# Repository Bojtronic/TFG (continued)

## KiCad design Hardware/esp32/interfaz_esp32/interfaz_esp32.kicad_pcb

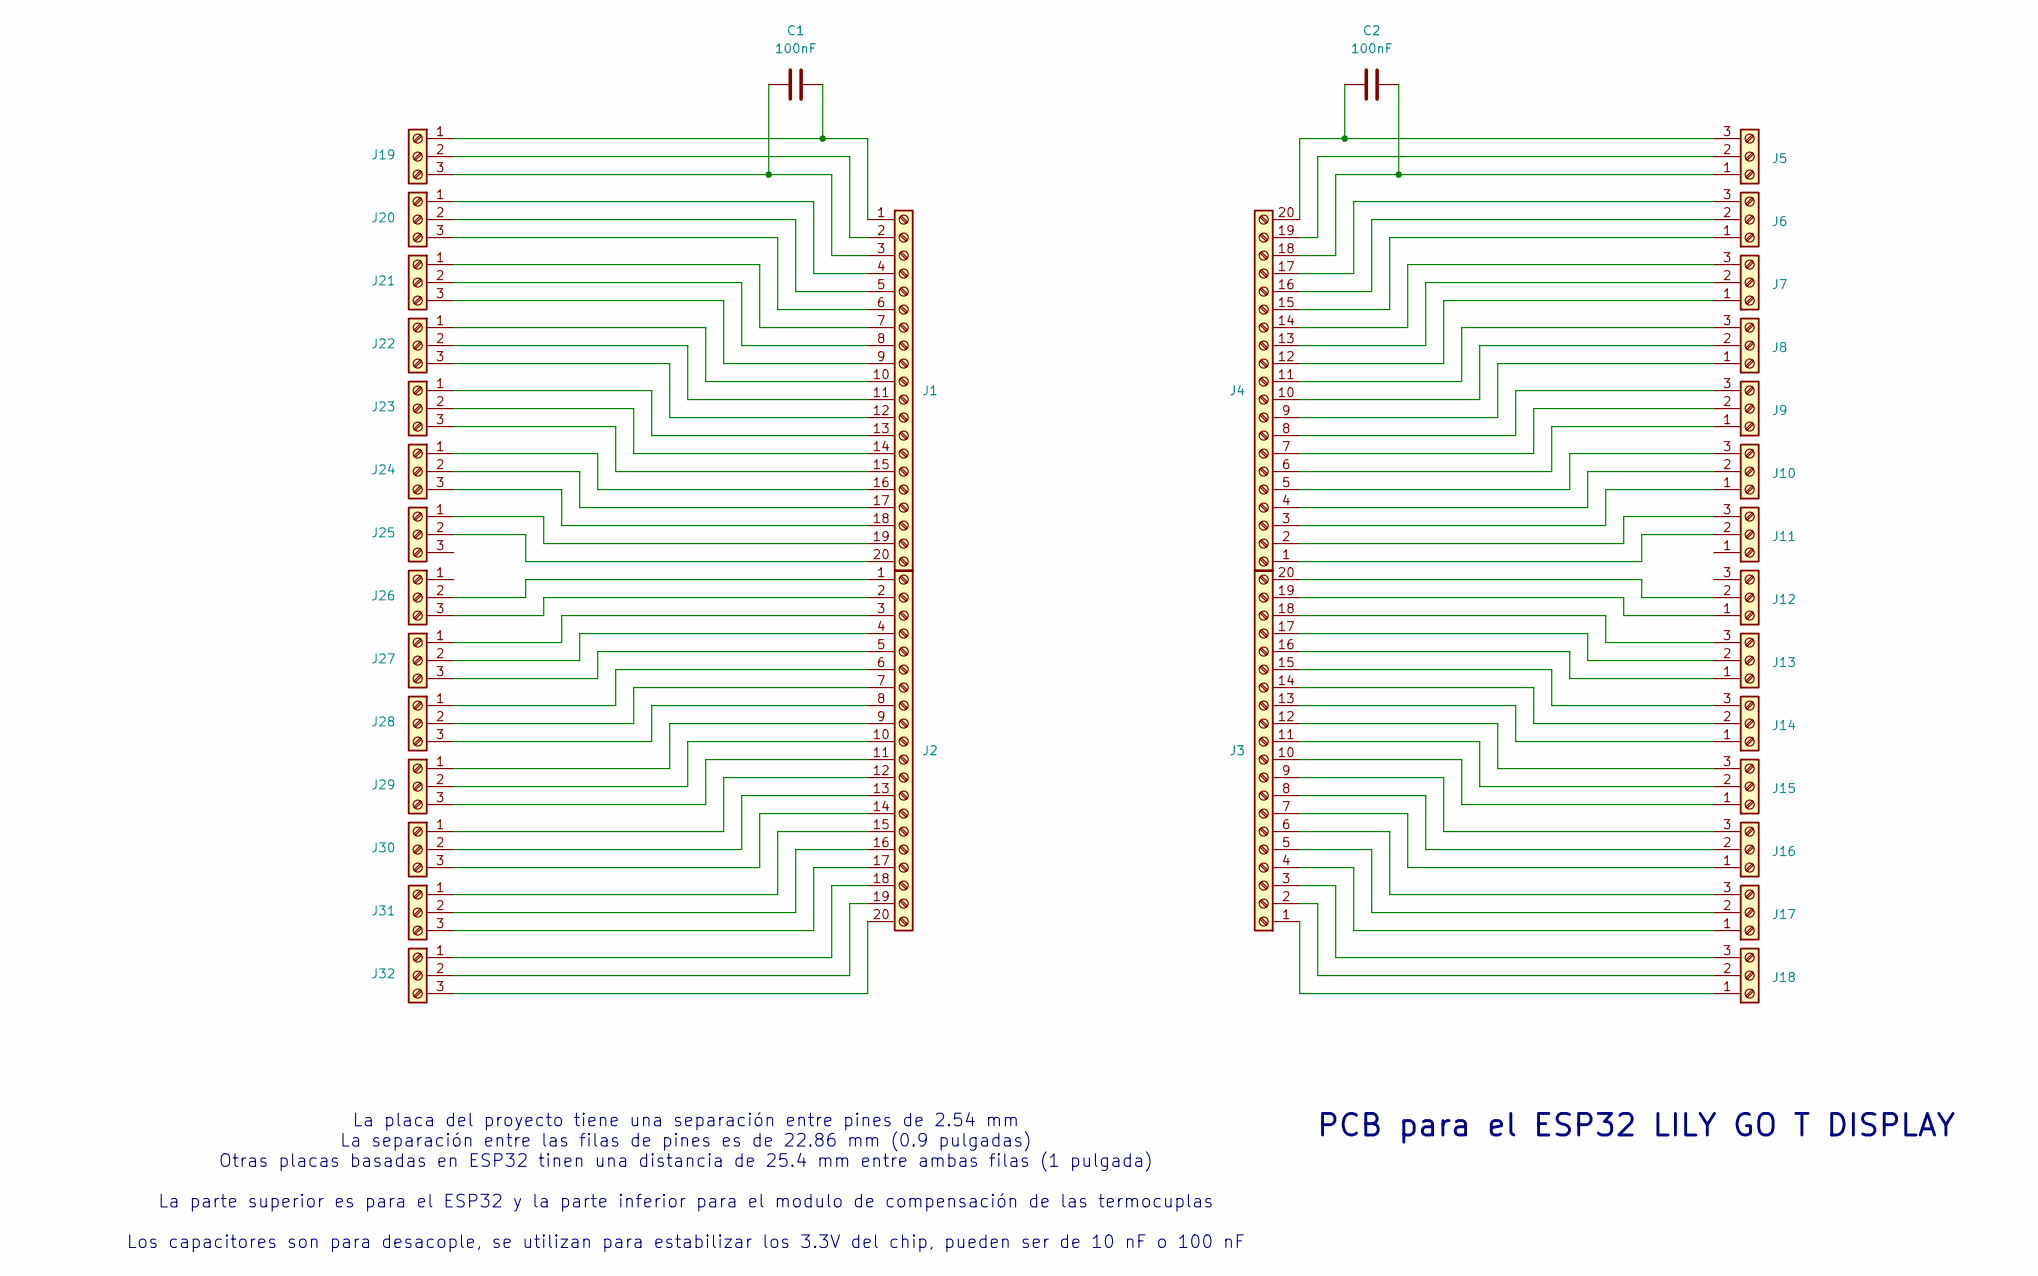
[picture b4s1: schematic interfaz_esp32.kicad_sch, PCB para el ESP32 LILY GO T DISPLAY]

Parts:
C1, C2: 100nF; C_Disc_D4.3mm_W1.9mm_P5.00mm
J1, J2, J3, J4: Screw_Terminal_01x20; PinHeader_1x20_P2.54mm_Vertical
J5, J6, J7, J8, J9, J10, J11, J12, J13, J14, J15, J16, J17, J18, J19, J20, J21, J22, J23, J24, J25, J26, J27, J28, J29, J30, J31, J32: Screw_Terminal_01x03; TerminalBlock_Phoenix_PT-1,5-3-3.5-H_1x03_P3.50mm_Horizontal

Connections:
unnamed: C1.1, J1.1, J19.1
unnamed: J1.2, J19.2
unnamed: C1.2, J1.3, J19.3
unnamed: J1.4, J20.1
unnamed: J1.5, J20.2
unnamed: J1.6, J20.3
unnamed: J1.7, J21.1
unnamed: J1.8, J21.2
unnamed: J1.9, J21.3
unnamed: J1.10, J22.1
unnamed: J1.11, J22.2
unnamed: J1.12, J22.3
unnamed: J1.13, J23.1
unnamed: J1.14, J23.2
unnamed: J1.15, J23.3
unnamed: J1.16, J24.1
unnamed: J1.17, J24.2
unnamed: J1.18, J24.3
unnamed: J1.19, J25.1
unnamed: J1.20, J25.2
unnamed: J2.1, J26.2
unnamed: J2.2, J26.3
unnamed: J2.3, J27.1
unnamed: J2.4, J27.2
unnamed: J2.5, J27.3
unnamed: J2.6, J28.1
unnamed: J2.7, J28.2
unnamed: J2.8, J28.3
unnamed: J2.9, J29.1
unnamed: J2.10, J29.2
unnamed: J2.11, J29.3
unnamed: J2.12, J30.1
unnamed: J2.13, J30.2
unnamed: J2.14, J30.3
unnamed: J2.15, J31.1
unnamed: J2.16, J31.2
unnamed: J2.17, J31.3
unnamed: J2.18, J32.1
unnamed: J2.19, J32.2
unnamed: J2.20, J32.3
unnamed: J4.6, J9.1
unnamed: J4.7, J9.2
unnamed: J4.8, J9.3
unnamed: J4.9, J8.1
unnamed: J4.10, J8.2
unnamed: J4.11, J8.3
unnamed: J4.12, J7.1
unnamed: J4.13, J7.2
unnamed: J4.14, J7.3
unnamed: J4.15, J6.1
unnamed: J4.16, J6.2
unnamed: J4.17, J6.3
unnamed: C2.1, J4.18, J5.1
unnamed: J4.19, J5.2
unnamed: C2.2, J4.20, J5.3
unnamed: J4.3, J10.1
unnamed: J4.4, J10.2
unnamed: J4.5, J10.3
unnamed: J4.1, J11.2
unnamed: J4.2, J11.3
unnamed: J3.19, J12.1
unnamed: J3.20, J12.2
unnamed: J3.16, J13.1
unnamed: J3.17, J13.2
unnamed: J3.18, J13.3
unnamed: J3.13, J14.1
unnamed: J3.14, J14.2
unnamed: J3.15, J14.3
unnamed: J3.10, J15.1
unnamed: J3.11, J15.2
unnamed: J3.12, J15.3
unnamed: J3.7, J16.1
unnamed: J3.8, J16.2
unnamed: J3.9, J16.3
unnamed: J3.4, J17.1
unnamed: J3.5, J17.2
unnamed: J3.6, J17.3
unnamed: J3.1, J18.1
unnamed: J3.2, J18.2
unnamed: J3.3, J18.3

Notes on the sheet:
PCB para el ESP32 LILY GO T DISPLAY
La placa del proyecto tiene una separación entre pines de 2.54 mm La separación entre las filas de pines es de 22.86 mm (0.9 pulgadas) Otras placas basadas en ESP32 tinen una distancia de 25.4 mm entre ambas filas (1 pulgada) La parte superior es para el ESP32 y la parte inferior para el modulo de 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

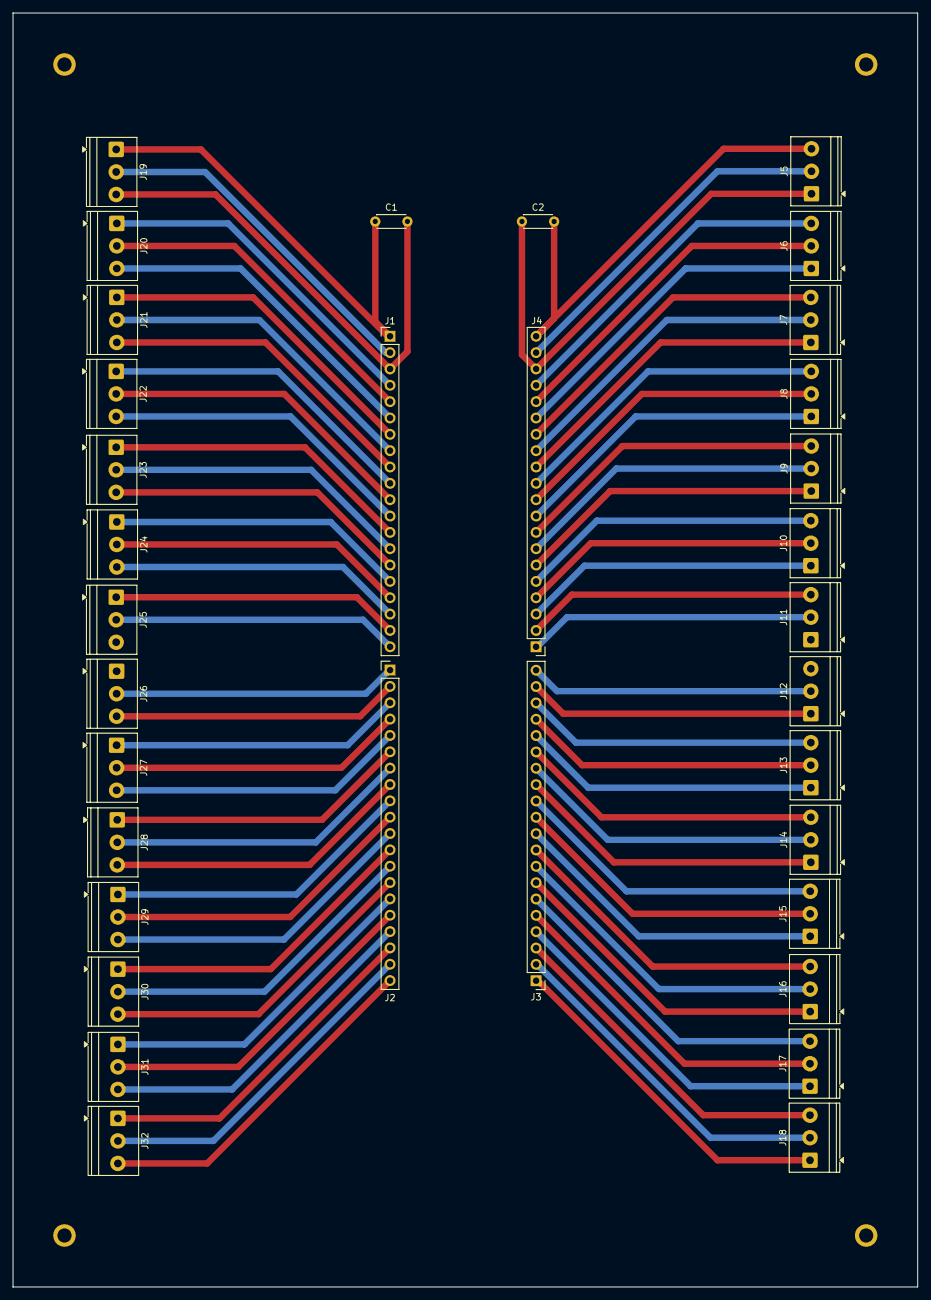
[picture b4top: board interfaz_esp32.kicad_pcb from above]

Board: 2 copper layers, 140.6 x 198.0 mm, 34 parts (0 on the bottom side), 80 nets.

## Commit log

2025-08-05 Ejemplos de ESP32 y creacion de la interfaz para el dashboard del horno
2025-08-08 (Error) Usando ngx-mqtt
2025-08-09 Comunicacion entre Interfaz y ESP32 mediante el broker de EMQX (MQTT y Angular 17)
2025-08-09 Configuracion para hacer deploy en la nube (host render)
2025-08-09 Correccion para el deploy en la nube
2025-08-09 Instalación de http-server
2025-08-09 Ajuste de seguridad para el deploy en la nube
2025-08-10 Creacion de servidor usando express (node js) con la intencion de habilitar la comunicacion en render
2025-08-10 Agregando dependencias que faltaban
2025-08-10 Quitando uso del servidor en express
2025-08-11 Modificacón de la función doPublish() y cambios en la interfaz grafica
2025-08-11 Modificación de la función doPublish()
2025-08-11 Cambio de unsafePublish a publish
2025-08-11 Cambiando de nuevo de Publish() a unsafePublish()
2025-08-13 Codigo base para el horno de secado de transformadores
2025-08-19 Datos de arduino cloud
2025-08-19 Configuracion para arduino cloud (en proceso)
2025-08-25 Ejemplo funcional de ESP32 con Arduino cloud
2025-08-26 Configuracion para Arduino Cloud (Se debe utilizar el servicio de API KEY el cual es de pago)
2025-08-29 Codigo de referencia
2025-09-05 Primera propuesta de codigo para el ESP32 (verificar compilacion y tamaño)
2025-09-08 Corrección de errores al codigo del esp32
2025-09-08 Quitar el EMO del sistema
2025-09-08 Optimizando codigo del esp32
2025-09-09 Optimizando codigo
2025-09-10 Inicio de los diagramas para las interfaces hardware
2025-09-12 Codigo para las termocuplas
2025-09-13 Creación del servidor y el cliente (control) con node js
2025-09-13 Actualización de servidor y clliente, incluye prueba de comunicacion desde el esp32
2025-09-13 Link del servidor en la nube
2025-09-13 Actualización del servidor
2025-09-13 Unificando servidor y cliente
2025-09-14 Unificando server y cliente
2025-09-14 Corrección de la función sendCommand()
2025-09-14 Simulación de transmision de datos entre el servidor y el ESP32
2025-09-14 Detalles estéticos
2025-09-15 Interfaz analógica
2025-09-15 Referencias a los componentes de los circuitos
2025-09-16 Footprint para el LM741
2025-09-16 Primera versión de la PCB para la interfaz analógica
2025-09-17 Lectura de la temperatura en la aplicación web
2025-09-17 Lectura de presión en la aplicación web
2025-09-17 Actualización del codigo del ESP32
2025-09-20 Conexion del harware para los sensores y los actuadores
    Inicio de la maquina de estados finitos
2025-09-20 FSM terminada pero falta verificar el funcionamiento
2025-09-23 Actualización de interfaz y comandos enviados
2025-09-23 Actualización de interfaz
2025-09-23 Archivos para pruebas
2025-09-24 Pruebas mejoradas con varios casos para cada estado
2025-09-24 Pruebas exitosas para los cambios de estado usando la aplicación web y los pulsadores, simulando los datos de los sensores para inducir estados funcionales (PROCESANDO, DETENER y MANUAL
2025-09-24 Comunicación con la aplicación web: se envian o se reciben datos cada 3 segundos
2025-09-25 Mensajes de estado
2025-09-25 Debug para el codigo de mensaje
2025-09-25 Mejorando estilo de advertencia grave
2025-09-25 Mejorando estilo de emergencia grave
2025-09-26 Habilitar los switches para los actuadores unicamente para el estado MANUAL
2025-09-26 Mejora visual para los switches en el estado MANUAL y demas estados
2025-09-26 Estilo para la advertencia de switches en estado MANUAL
2025-09-26 Advertencia de switches en estado MANUAL
2025-09-26 Estilos para los botones de estados
2025-09-26 Mejorar para el envio de comandos en estado MANUAL
2025-09-26 Mejoras para el envio de comandos en estado MANUAL
2025-09-27 Información sobre la activacion/desactivacion de actuadores
2025-09-30 Corrección para el mensaje de alerta en estado manual
2025-09-30 Trabajando en el PCB de señales digitales
2025-10-01 Creación de PCB's con los archivos gerber y drill
2025-10-01 Actualización de la lectura para los sensores de nivel de agua en el tanque
2025-10-01 Eliminación de codigo innecesario
2025-10-02 PCB para el ESP32
2025-10-02 Pruebas con archivo de simulación y lectura de sensores
2025-10-03 Capacitores de desacople
2025-10-03 Interfaz de la HMI
2025-10-03 Trabajando en la HMI
2025-10-04 HMI lista para pruebas
2025-10-04 Pruebas con HMI
2025-10-04 Esquematicos de las PCB
2025-10-07 Recursos para la documentación
2025-10-07 Visualización de datos en HMI
2025-10-07 Actuallizando HMI
2025-10-07 Gestion de la comunicación UART del HMI
2025-10-08 Mejoras en la comunicación del HMI
2025-10-08 Imagen de la interfaz del HMI
2025-10-08 Se crean variables que almacenan valores anteriores para optimizar la comunicación
2025-10-08 Optimización de la función checkForCommands()
2025-10-08 Optimización de la función connectToWiFi()
2025-10-08 Ajustes en la comunicación
2025-10-09 Pruebas al prototipo con todo integrado BOD (los sensores de presion y nivel se simularon con fuentes)
2025-10-11 Imagenes para la documentación
2025-10-12 Agregando agujeros para montaje a las PCB
2025-10-12 Ruteo de la interfaz analógica
2025-10-12 Informe semi-terminado
2025-10-13 Eliminación de archivos innecesarios
2025-10-13 Comentando codigo para debug (Serial.print())
2025-10-14 Iniciando una PCB que integre todos los modulos
2025-10-14 Integrando todas las interfaces
2025-10-14 Reorganizando elementos
2025-10-15 Integración de nuevos modulos al PCB (puente H, detector de cruce por cero, disparo con triac, salida analogica amplificada)
2025-10-16 Corrección de funciones de verificarSeguridad y detenerSistema
2025-10-16 Integrando nuevos modulos al PCB
2025-10-17 Actualización de PCB
2025-10-17 Versión preliminar del PCB
2025-10-17 Esquematico listo
2025-10-18 Reorganización del esquematico
2025-10-18 Organizando elementos en PCB
2025-10-19 Actualización de esquematico
2025-10-20 Agregando diodos de rueda libre (flyback)
2025-10-20 PCB preliminar
2025-10-20 Esquematico definitivo
2025-10-21 Layout del PCB
2025-10-21 Ruteo
2025-10-22 Ruteo de PCB
2025-10-22 Archivos de fabricación .gerber y .drl
2025-10-22 Archivos para fabricación .gbr y .drl
2025-10-23 Ajuste de pads
2025-10-23 Corrección de ruteo
2025-10-23 Ajustes a las interfaces digital y analogica
2025-10-25 Listado de componentes para el PCB
2025-10-28 Mensaje de WhatsApp
2025-10-29 Configuración para mensajes de WhatsApp
2025-11-01 Imagenes del osciloscopio
2025-11-01 Imagenes para el informe
2025-11-03 Informe final v1
2025-11-21 Pruebas exitosas con PCB para las entradas digitales
2025-11-26 Pruebas exitosas con PCB para la entrada analógica
2025-12-02 Pruebas con temperatura: termocupla 2 no se detecta
2025-12-02 Prueba con pin 32 para termocupla 2: aun no se lee la termperatura de la termocupla 2
2026-01-21 Lista de componentes en el formato de Digicontrol
